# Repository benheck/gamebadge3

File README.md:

gamebadge 3 Midwest Gaming Classic workshop project

Some existing Catskill games may not be able to save without a /save folder in the MSD USB root directory, add a "save" folder to enable.

Build procedure:
https://www.youtube.com/watch?v=VSEMkjyJ5Pk

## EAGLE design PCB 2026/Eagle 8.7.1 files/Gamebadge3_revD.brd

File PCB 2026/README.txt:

Slight changes based on the 2023 workshop experience
Plan is to have PCBway make these and populate the boring stuff

Have class do audio amp, tact, through hole and PICO

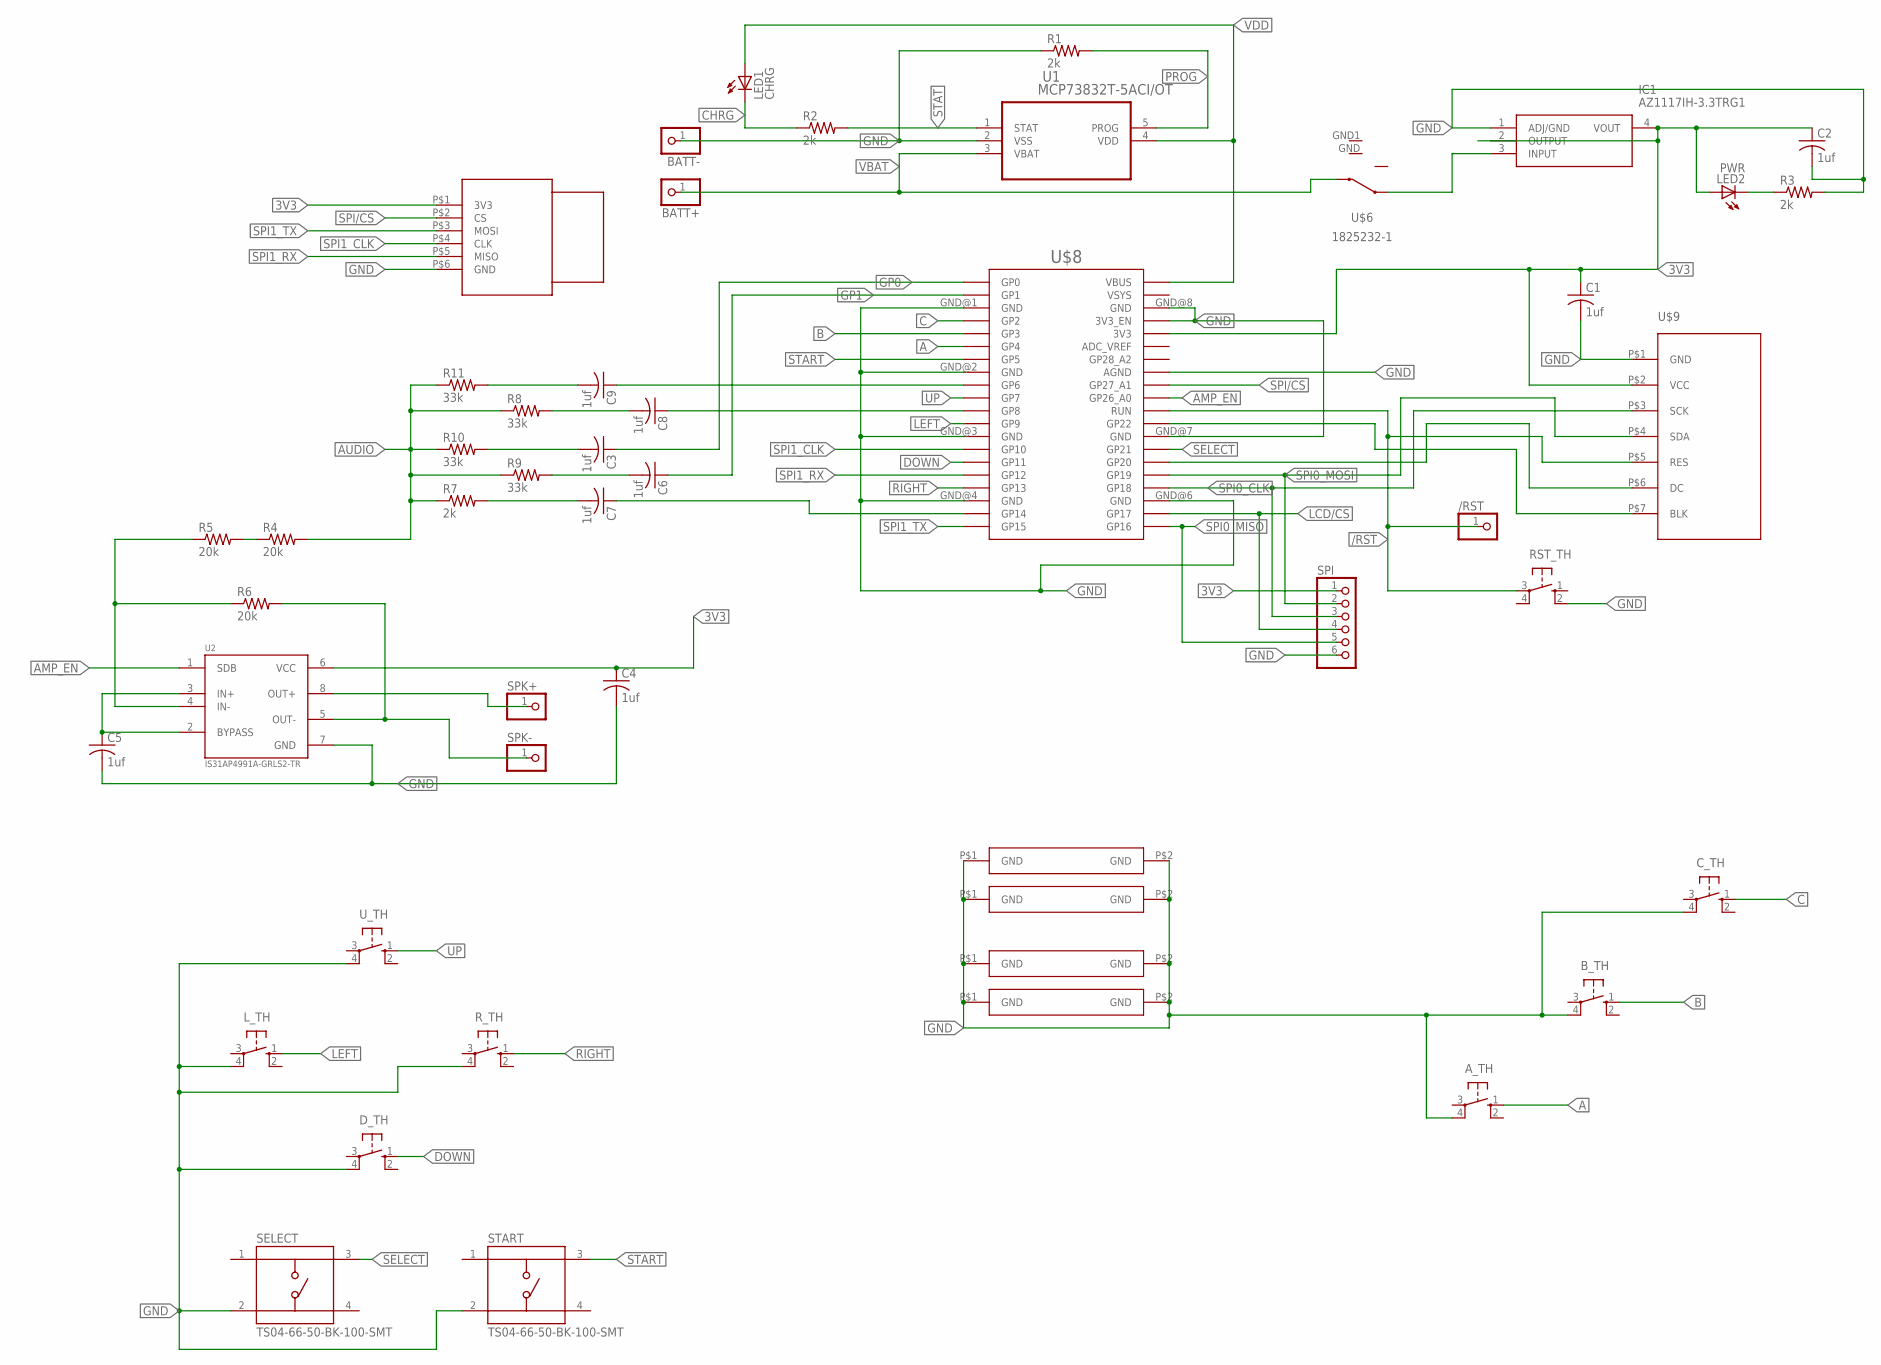
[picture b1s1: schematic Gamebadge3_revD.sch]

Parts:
/RST: PINHD-1X1; 1X01
A_TH: 10-XX; B3F-10XX
BATT+: PINHD-1X1; 1X01
BATT-: PINHD-1X1; 1X01
B_TH: 10-XX; B3F-10XX
C1, C2, C3, C4, C5, C6, C7, C8, C9: 1uf; C0805
C_TH: 10-XX; B3F-10XX
D_TH: 10-XX; B3F-10XX
IC1: AZ1117IH-3.3TRG1; SOT230P700X170-4N
LED1: CHRG; LED3MM
LED2: PWR; LED3MM
L_TH: 10-XX; B3F-10XX
R1, R2, R3, R7: 2k; R0805
R4, R5, R6: 20k; R0805
R8, R9, R10, R11: 33k; R0805
RST_TH: 10-XX; B3F-10XX
R_TH: 10-XX; B3F-10XX
SELECT: TS04-66-50-BK-100-SMT; SW_TS04-66-50-BK-100-SMT
SPI: PINHD-1X6; 1X06
SPK+: PINHD-1X1; 1X01
SPK-: PINHD-1X1; 1X01
START: TS04-66-50-BK-100-SMT; SW_TS04-66-50-BK-100-SMT
U1: MCP73832T-5ACI/OT; SOT95P300X145-5N
U2: IS31AP4991A-GRLS2-TR; SOIC127P604X170-8N
U$1: SD_CARD_ADAPTER; SD_CARD
U$2, U$3, U$4, U$5: GND_CLIP
U$6: 1825232-1
U$8: RPI_PICO_W
U$9: ST7789
U_TH: 10-XX; B3F-10XX

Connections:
3V3: C1.1, C2.1, C4.1, IC1.2 (OUTPUT), IC1.4 (VOUT), LED2.A, SPI.1, U2.6 (VCC), U$1.P$1 (3V3), U$8.3V3, U$9.P$2 (VCC)
/RST: /RST.1, RST_TH.3, U$8.RUN, U$9.P$5 (RES)
A: A_TH.1 (S), U$8.GP4
AMP_EN: U2.1 (SDB), U$8.GP26_A0
AUDIO: R4.2, R7.1, R8.1, R9.1, R10.1, R11.1
B: B_TH.1 (S), U$8.GP3
C: C_TH.1 (S), U$8.GP2
CHRG: LED1.K (C), R2.1
DOWN: D_TH.1 (S), U$8.GP11
GND: A_TH.4 (P1), BATT-.1, B_TH.4 (P1), C1.2, C2.2, C4.2, C5.2, C_TH.4 (P1), D_TH.4 (P1), IC1.1 (ADJ/GND), L_TH.4 (P1), R1.1, R3.2, RST_TH.2 (S1), R_TH.4 (P1), SELECT.2, SPI.6, START.2, U1.2 (VSS), U2.7 (GND), U$1.P$6 (GND), U$2.P$1, U$2.P$2, U$3.P$1, U$3.P$2, U$4.P$1, U$4.P$2, U$5.P$1, U$5.P$2, U$8.3V3_EN, U$8.AGND, U$8.GND@1 (GND), U$8.GND@2 (GND), U$8.GND@3 (GND), U$8.GND@4 (GND), U$8.GND@6 (GND), U$8.GND@7 (GND), U$8.GND@8 (GND), U$9.P$1 (GND), U_TH.4 (P1)
GP0: C3.1, U$8.GP0
GP1: C6.1, U$8.GP1
LCD/CS: SPI.4, U$8.GP17
LEFT: L_TH.1 (S), U$8.GP9
unnamed: C5.1, U2.2 (BYPASS), U2.3 (IN+)
unnamed: U$8.GP20, U$9.P$6 (DC)
unnamed: R4.1, R5.2
unnamed: U$8.GP22, U$9.P$7 (BLK)
unnamed: R5.1, R6.1, U2.4 (IN-)
unnamed: IC1.3 (INPUT), U$6.3
unnamed: R6.2, SPK-.1, U2.5 (OUT-)
unnamed: LED2.K (C), R3.1
unnamed: SPK+.1, U2.8 (OUT+)
unnamed: C7.1, U$8.GP14
unnamed: C6.2, R9.2
unnamed: C7.2, R7.2
unnamed: C8.1, U$8.GP8
unnamed: C8.2, R8.2
unnamed: C3.2, R10.2
unnamed: C9.1, U$8.GP6
unnamed: C9.2, R11.2
PROG: R1.2, U1.5 (PROG)
RIGHT: R_TH.1 (S), U$8.GP13
SELECT: SELECT.3, U$8.GP21
SPI0_CLK: SPI.3, U$8.GP18, U$9.P$3 (SCK)
SPI0_MISO: SPI.5, U$8.GP16
SPI0_MOSI: SPI.2, U$8.GP19, U$9.P$4 (SDA)
SPI1_CLK: U$1.P$4 (CLK), U$8.GP10
SPI1_RX: U$1.P$5 (MISO), U$8.GP12
SPI1_TX: U$1.P$3 (MOSI), U$8.GP15
SPI/CS: U$1.P$2 (CS), U$8.GP27_A1
START: START.3, U$8.GP5
STAT: R2.2, U1.1 (STAT)
UP: U$8.GP7, U_TH.1 (S)
VBAT: BATT+.1, U1.3 (VBAT), U$6.2
VDD: LED1.A, U1.4 (VDD), U$8.VBUS

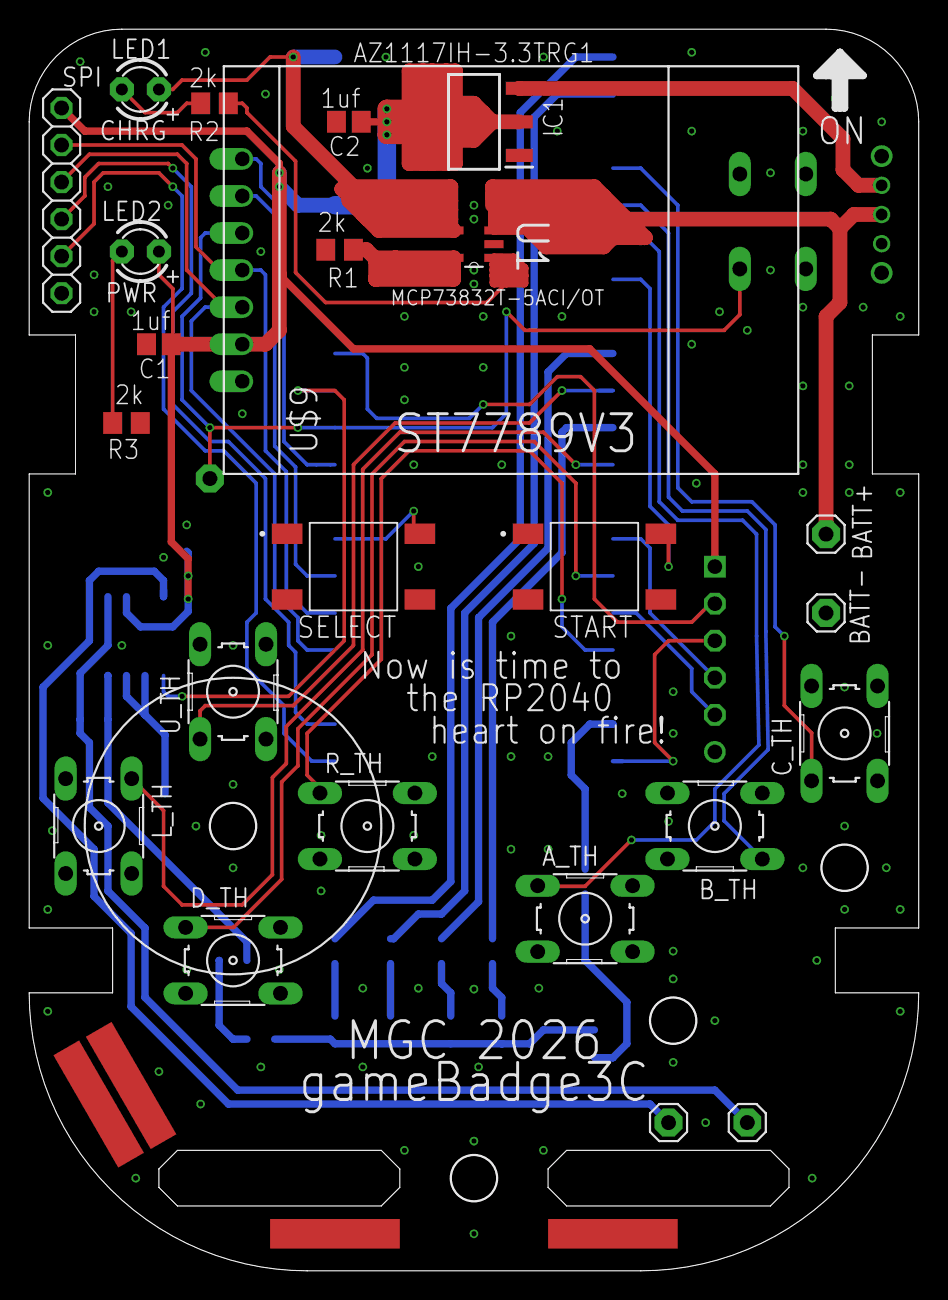
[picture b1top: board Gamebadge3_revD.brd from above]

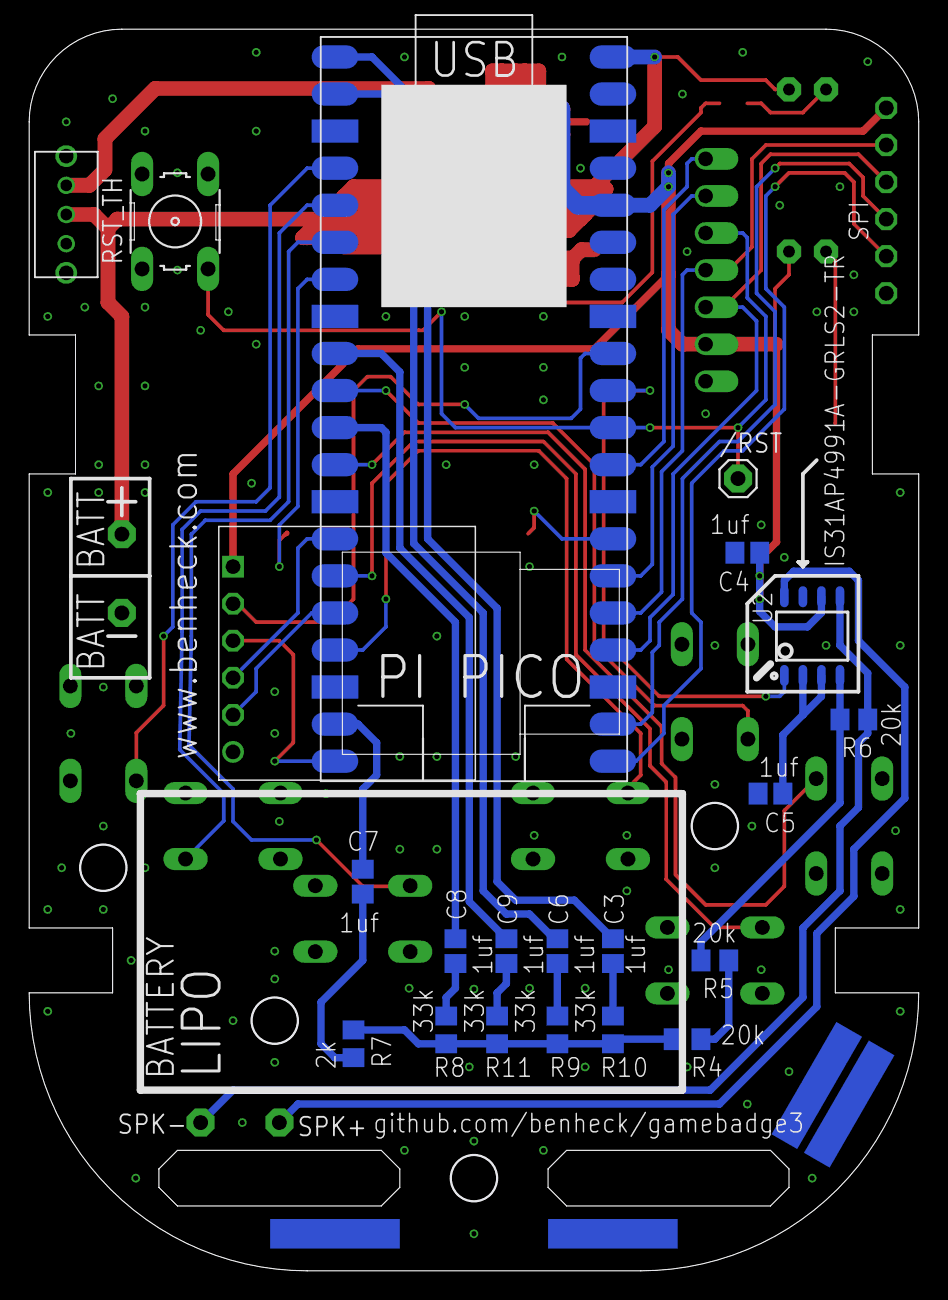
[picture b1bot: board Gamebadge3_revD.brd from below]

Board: 2 copper layers, 60.8 x 84.9 mm, 49 parts (21 on the bottom side), 46 nets.

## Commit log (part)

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2023-01-02 Sorting stuff
2023-01-04 added amps to try
2023-01-07 Fix for the scroll glitch I hope
2023-01-07 Added Grevious as a sample game
2023-01-07 Larger map for scroll testing & some additional tiles
2023-01-07 Added work wrap and button debounce
2023-01-09 Fixed issue with custom palette not being used
2023-01-09 Added individual tile palettes, and removed button debouncing code (now done in game library)
2023-01-10 Adding sprite flipping, fixed sprite transparency glitch
2023-01-11 Grevious Update - Added status bar and title screen
2023-01-21 Added more code
2023-01-29 Adding stuff
2023-01-30 Updates to grevious
2023-02-04 Added objects and hitboxes
2023-02-04 Removed audio PIO references
2023-02-04 Added screen bracket and peg
2023-02-05 More game coding
2023-02-06 Adding menus and state machines, getTile function
2023-02-12 Working on game
2023-02-13 Added features
2023-02-14 Added PCBs
2023-02-15 Arranged folders and changed case STL
2023-02-19 Map editor, added file commands
2023-02-20 Added file features
2023-02-20 Adding tiles
2023-03-04 Code work
2023-03-04 Code stuff
2023-03-06 Added waveform generator and sample app - NES Jukebox
2023-03-07 Fixed a volume leveling bug
2023-03-07 Cat game updates
2023-03-08 Bud damage and robot collision
2023-03-11 Adding more SFX
2023-03-12 Code tweaks
2023-03-15 Updated audio library with file streaming and NESJukebox example app
2023-03-22 Bud game. Also added stopMusic in gamebadge library
2023-03-23 Added "No files" boot font
2023-03-23 Badgeris v1 release
2023-03-24 Fixed a couple of bugs
2023-03-24 Working on Bud cutscenes
2023-03-24 Added GBAudio library
2023-03-25 Again changes to hell
2023-03-26 Added PCM data
2023-03-26 Changes to PWM and GBAdudio
2023-03-26 Fixed GLACK
2023-03-26 Save/load files
2023-03-27 Implemented smaller play queue
2023-03-27 Changed volume scaling in GB audio
2023-03-27 Fixing critical bugs 4 days before release
2023-03-27 Burn-in Bud test
2023-03-28 Added PAWS function
2023-03-29 Polish sausage
2023-03-29 Updated GBaudio
2023-03-29 Badgeris updates - added more music, SFX option, and high score table
2023-03-30 More tweaks and bug fixes
2023-03-30 Mac glitch fix?
2023-03-30 Room 1-3 fix
2023-03-31 Pre MGC commit
2023-03-31 Badgeris update... title screen, high score save, line animations, and color corrections
2023-04-04 Added OSHpark Gerber files
2023-04-05 Added parts lists
2023-04-05 Updated screen bracket
2023-04-05 Added button covers
2023-07-17 Removed DMA GPIO flags and moved folders around
2023-08-07 New case and organzing
2023-08-11 New case
2023-09-05 Added descriptor
2023-12-25 Updated design 2024 for SD card
2023-12-30 Added support for updated 2024 version of the board
2024-01-19 Updated PCB version 3B
2024-01-19 Updated audio library for version 3B
2024-01-19 Added Badgeris for gameBadge3B
2024-01-19 Added missing prototype functions
2024-02-07 Update gameBadgePico.cpp
    avoid DMA collision with new LCD commands
2024-02-09 add README
2024-02-11 Update README.md
    Update README.md
2024-02-24 Improve screen stability by insuring there is a 1µs delay after a dma transfer is done before starting a new one. This modification insure that there is no collision with a previous block, so the pre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
    A few other modifications have been made removing some constants and uselesss calls.
2024-02-25 Before starting a new DMA cycle, we need to wait that the previous DMA is finished AND that the SPI is empty !
2024-02-25 Clean code, remove unneeded state
2024-02-25 Remove README for PR
2024-02-28 Added new case
2024-03-23 Added HardwareTester App
2024-03-26 Updated NES Jukebox for 3B
2024-03-26 Updated NESJukebox, precompiled catskill, added a couple emulators, and program loader
2024-03-27 Added Atari 800 emulator
2024-03-29 Added alternate rear case
2024-03-30 Added Coleco Vision Emulator
2024-03-30 Clean up old emu files
2024-03-30 Added Atari 5200 Emulator
2024-04-01 Added Odyssey 2 Emulator
2024-04-04 Added Gameboy emulator and Badgeris source
2024-04-05 Added assembly doc
2024-04-05 Updated loader
2024-04-20 readme changes
2024-07-17 Added Amazon link for the LCD
2025-11-01 Added support for ST7789V3. Cat game has 3 gamebadge selects at start of code. Changes to gamebadge and pico ST7789 libs. Still compatible with older Gamebadges. I hope!
2025-11-07 Added save folder to base file system
2025-11-07 Initialize README with project details
    Added project description and build procedure link.
2025-12-30 Updated case for 2026 design (ST7789rev3 LCD)
2026-02-01 Updated PCB for production
2026-02-15 Changed case for clips
2026-03-24 Added Screen Bracket for 2026 workshop
2026-04-07 Release of new 2026 GameBoy Emulator
2026-04-07 Added NES emulator
2026-04-07 Updated audio in emulators
2026-04-07 NES Emulator updates - swapped buttons, and supports 1024 ROMs in file browser
2026-04-11 Added bootloader and updated a couple emulators
2026-04-11 Added 2026 games/programs
2026-04-11 Updated bootloader
